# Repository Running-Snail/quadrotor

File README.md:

# Quadrotor
迷你四旋翼

## steps
1. 用nano板接电机，接MOFSET管，接3.7v电压，PWM测试
    1. 测试用MOFSET管（把面包线焊到三个引脚上）√ 3.7v下转动 1.13A N沟道
    2. 编写一路测试PWM（程序硬编码一个特定的百分比值）√
    3. 电池测试 √
2. 测试多路PWM和空心杯驱动（与下一步画电路板同时进行）
    1. 4路PWM驱动电机测试
    2. 电池驱动测试
    3. 蓝牙通讯（制定协议√，电脑或者手机端蓝牙传输通讯）
    4. 蓝牙协议，avr端实现 √
    5. avr端实现优化
    6. 蓝牙协议，android端实现
3. 画电路板（测试板，开发板）
    1. 初步电路√，万用板搭建实验
    2. 购买芯片（估计要买很多，以供下面的步骤使用）
    3. 焊接芯片
    4. 调试 -> 改正
4. 四旋翼结构设计
    1. 程序模拟（这个不太了解怎么模拟）
    2. 做一个模型进行测试
5. 画正式四旋翼电路板
    1. 焊接芯片
    2. 调试 -> 改正

## 蓝牙协议
接收bytes序列
序列格式

```
| pkg byte | pkg byte2 (optional) | ... | data len byte ( use 7 bits ) | data len byte 2 (optional) | ... | actual data | xor check sum |
```

```
pkgs
HELLO 0x48
SET_MOTOR 0x53
FEEDBACK 0x41
ERROR 0x45 
```

```
ERROR types
buffer_overflow 0x1
```

### SET_MOTOR 设置电机转速
设置电机1的转速为128

```
| 0x53 | 0x02 | 0x00 | 0x80 | 0xd1 |
```

### HELLO 包
```
| 0x48 | 0x0 | 0x48 | 
```

### OK 回执
```
| 0x41 | 0x2 | 0x6f | 0x6b | 0x47 |
```

## notes
* 720空心杯3.7v电压下转动 电流测得1.13A
* 笔记本usb的电流不够大，空心杯转起来了之后就没有额外的电流提供给蓝牙模块了，使用锂电池解决这个问题
* 电机转速太快的情况下会对蓝牙模块产生电磁干扰（怀疑，还需证实，需要在电机壳上加电容）
* 电路原理图
    * atmega328p最小系统
        * 晶振电路 √
        * reset按键 √
        * 电源开关 电源灯 电源插头 √
        * 稳压电路 √
        * 滤波电容 √
        * 编程/运行开关 √
        * 编程接口 √
            * 使用arduino的bootloader
                * usb转串口 外置 留出RX TX 
            * SPI下载接口 √
    * 电机电路
        * 四路PWM N沟道 MOSFET电路 √
        * 电机及外壳电容电路（减弱磁场效应）
    * 通讯模块
        * 蓝牙模块接口 √
    * 电池固定结构

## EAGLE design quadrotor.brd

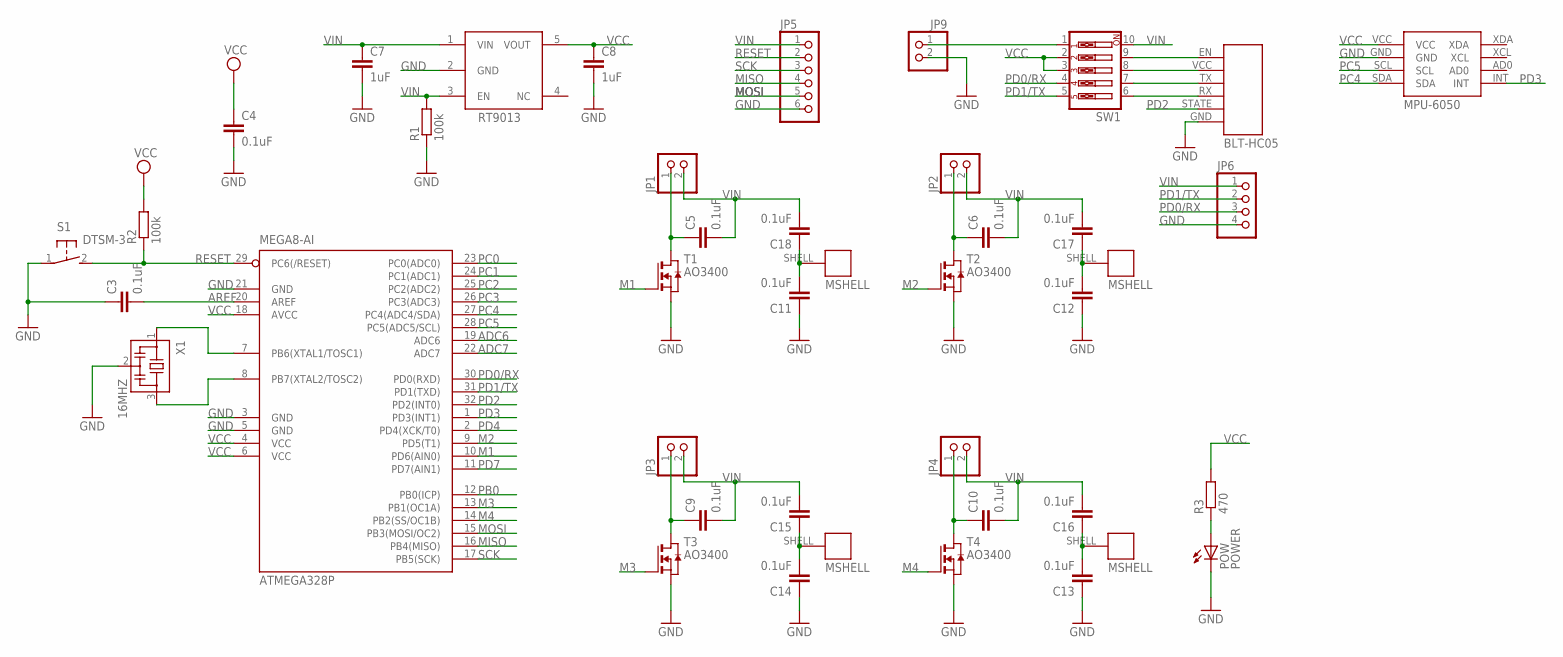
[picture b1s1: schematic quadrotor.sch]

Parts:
ATMEGA328P: MEGA8-AI; TQFP32-08
C3, C4, C5, C6, C9, C10, C11, C12, C13, C14, C15, C16, C17, C18: 0.1uF; C0603
C7, C8: 1uF; C0603
JP1, JP2, JP3, JP4, JP9: PINHD-1X2; 1X02
JP5: PINHD-1X6; 1X06
JP6: PINHD-1X4; 1X04
POW: POWER; LED_SML0603
R1, R2: 100k; R0603
R3: 470; R0603
S1: DTSM-3
SW1: SW_DIP-5; EDG-05
T1, T2, T3, T4: AO3400; SOT-23
U$1: RT9013; SOT-23-5
U$2: BLT-HC05
U$3, U$4, U$5, U$6: 720-MSHELL; 720MOTOR
U$7: MPU-6050
X1: 16MHZ; CSTCR6M

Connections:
ADC6: ATMEGA328P.19 (ADC6)
ADC7: ATMEGA328P.22 (ADC7)
AREF: ATMEGA328P.20 (AREF), C3.2
GND: ATMEGA328P.3 (GND), ATMEGA328P.5 (GND), ATMEGA328P.21 (GND), C3.1, C4.2, C7.2, C8.2, C11.1, C12.1, C13.1, C14.1, JP5.6, JP6.4, JP9.2, POW.C, R1.1, S1.1, T1.2 (S), T2.2 (S), T3.2 (S), T4.2 (S), U$1.2 (GND), U$2.GND, U$7.GND, X1.2
M1: ATMEGA328P.10 (PD6(AIN0)), T1.3 (G)
M2: ATMEGA328P.9 (PD5(T1)), T2.3 (G)
M3: ATMEGA328P.13 (PB1(OC1A)), T3.3 (G)
M4: ATMEGA328P.14 (PB2(SS/OC1B)), T4.3 (G)
MISO: ATMEGA328P.16 (PB4(MISO)), JP5.4
MOSI: ATMEGA328P.15 (PB3(MOSI/OC2)), JP5.5
unnamed: ATMEGA328P.7 (PB6(XTAL1/TOSC1)), X1.1
unnamed: ATMEGA328P.8 (PB7(XTAL2/TOSC2)), X1.3
unnamed: C14.2, C15.1, U$5.SHELL
unnamed: C5.1, JP1.1, T1.1 (D)
unnamed: C11.2, C18.1, U$3.SHELL
unnamed: C6.1, JP2.1, T2.1 (D)
unnamed: SW1.9, U$2.EN
unnamed: POW.A, R3.1
unnamed: C10.1, JP4.1, T4.1 (D)
unnamed: C9.1, JP3.1, T3.1 (D)
unnamed: SW1.8, U$2.VCC
unnamed: SW1.7, U$2.TX
unnamed: SW1.6, U$2.RX
unnamed: JP9.1, SW1.1
unnamed: C12.2, C17.1, U$4.SHELL
unnamed: C13.2, C16.1, U$6.SHELL
PB0: ATMEGA328P.12 (PB0(ICP))
PC0: ATMEGA328P.23 (PC0(ADC0))
PC1: ATMEGA328P.24 (PC1(ADC1))
PC2: ATMEGA328P.25 (PC2(ADC2))
PC3: ATMEGA328P.26 (PC3(ADC3))
PC4: ATMEGA328P.27 (PC4(ADC4/SDA)), U$7.SDA
PC5: ATMEGA328P.28 (PC5(ADC5/SCL)), U$7.SCL
PD0/RX: ATMEGA328P.30 (PD0(RXD)), JP6.3, SW1.4
PD1/TX: ATMEGA328P.31 (PD1(TXD)), JP6.2, SW1.5
PD2: ATMEGA328P.32 (PD2(INT0)), U$2.STATE
PD3: ATMEGA328P.1 (PD3(INT1)), U$7.INT
PD4: ATMEGA328P.2 (PD4(XCK/T0))
PD7: ATMEGA328P.11 (PD7(AIN1))
RESET: ATMEGA328P.29 (PC6(/RESET)), JP5.2, R2.1, S1.2
SCK: ATMEGA328P.17 (PB5(SCK)), JP5.3
VCC: ATMEGA328P.4 (VCC), ATMEGA328P.6 (VCC), ATMEGA328P.18 (AVCC), C4.1, C8.1, R2.2, R3.2, SW1.2, SW1.3, U$1.5 (VOUT), U$7.VCC
VIN: C5.2, C6.2, C7.1, C9.2, C10.2, C15.2, C16.2, C17.2, C18.2, JP1.2, JP2.2, JP3.2, JP4.2, JP5.1, JP6.1, R1.2, SW1.10, U$1.1 (VIN), U$1.3 (EN)

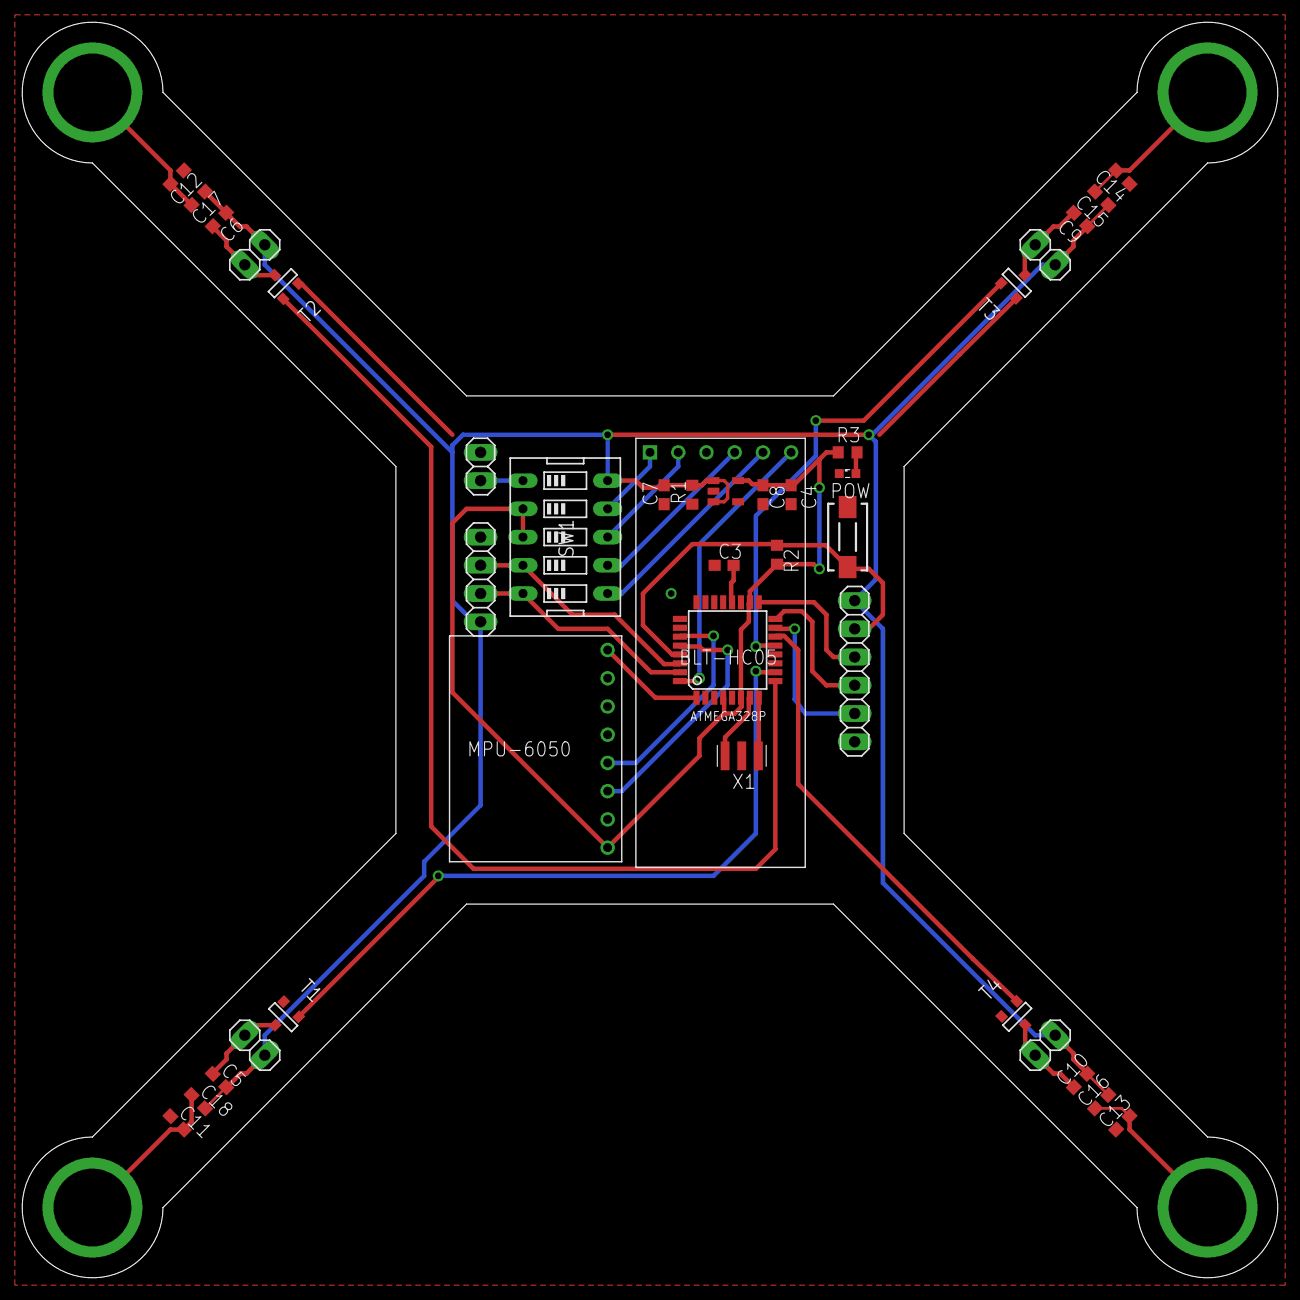
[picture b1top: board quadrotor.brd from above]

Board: 2 copper layers, 113.0 x 113.0 mm, 42 parts (0 on the bottom side), 34 nets.

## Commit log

2015-12-11 plan steps to win the battle
2015-12-26 done bluetooth protocal
2015-12-26 remove track backup files
2015-12-27 mostly done layout and is routing now
2015-12-29 basically done pcb layout
2016-01-07 basically done v1 brd
